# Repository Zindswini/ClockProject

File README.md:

# ClockProject V2.0
This is the GitHub Companion to the Large scale RGB LED Clock as shown in [VIDEO IN PROGRESS]

# Design Files
- 3D and Circuit design was completed using Autodesk Fusion 360. Exports from the project are provided.
- Manufacturing was completed through JLC PCB, Gerber files exported from Fusion 360 are provided.

# Dependencies & Building
This project uses PlatformIO to manage dependencies. In theory, this should mean that you will not have to worry about dependencies and versioning. Just in case, a list of used libraries is provided below.

In order to program your own clock, you need to provide the appropriate credentials for your Wifi network. In order to connect, update the STASSID and STAPSK fields.

This project relies on:
### Libraries:
- [Adafruit ESP8266](https://github.com/adafruit/Adafruit_ESP8266) (In Library Browser)
- [Arduino JSON](https://github.com/bblanchon/ArduinoJson/tree/5.x)  (In Library Browser) (*Note version 5.x*)
- [DHTesp](https://github.com/beegee-tokyo/DHTesp) (In Library Browser)
- [NTPClient](https://github.com/arduino-libraries/NTPClient) (In Library Browser)
- [TelnetStream](https://github.com/jandrassy/TelnetStream) (In Library Browser)

### ESP Board
Add http://arduino.esp8266.com/stable/package_esp8266com_index.json to the "Additional Board Manager URLs" in the Arduino IDE, then add the esp8266 from inside the board manager.

Be sure to select "Adafruit Feather HUZZAH ESP8266" when compiling.

(this might be obsolete now that the project uses PlatformIO)

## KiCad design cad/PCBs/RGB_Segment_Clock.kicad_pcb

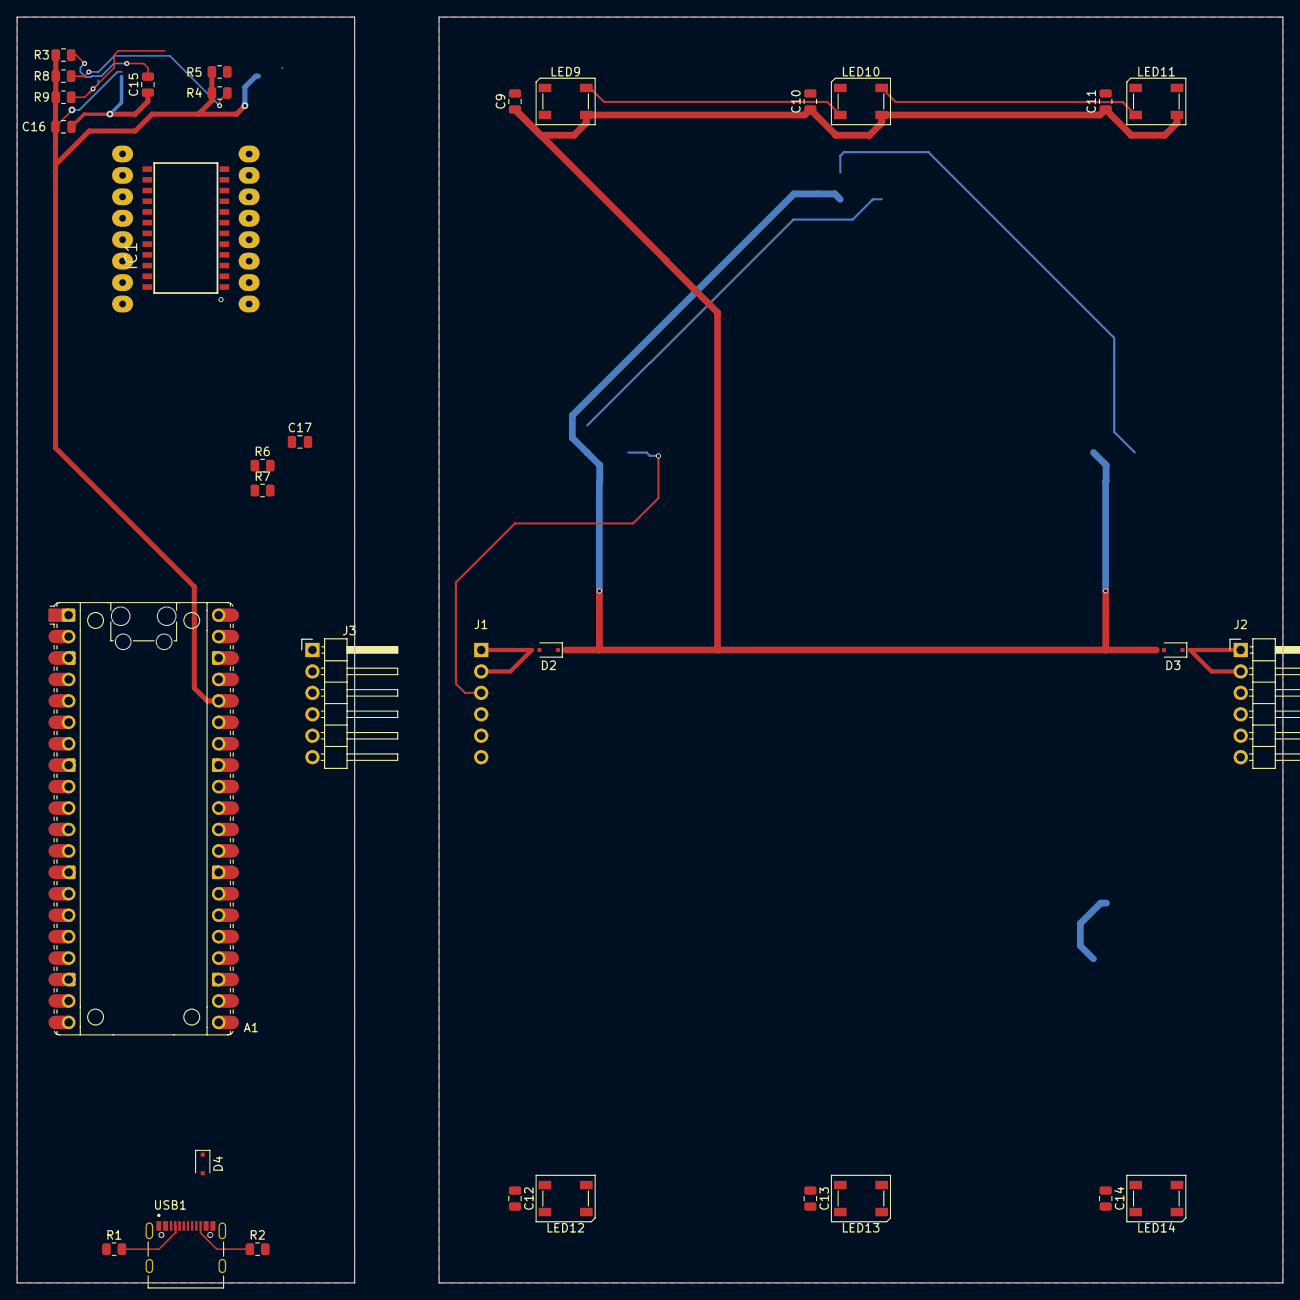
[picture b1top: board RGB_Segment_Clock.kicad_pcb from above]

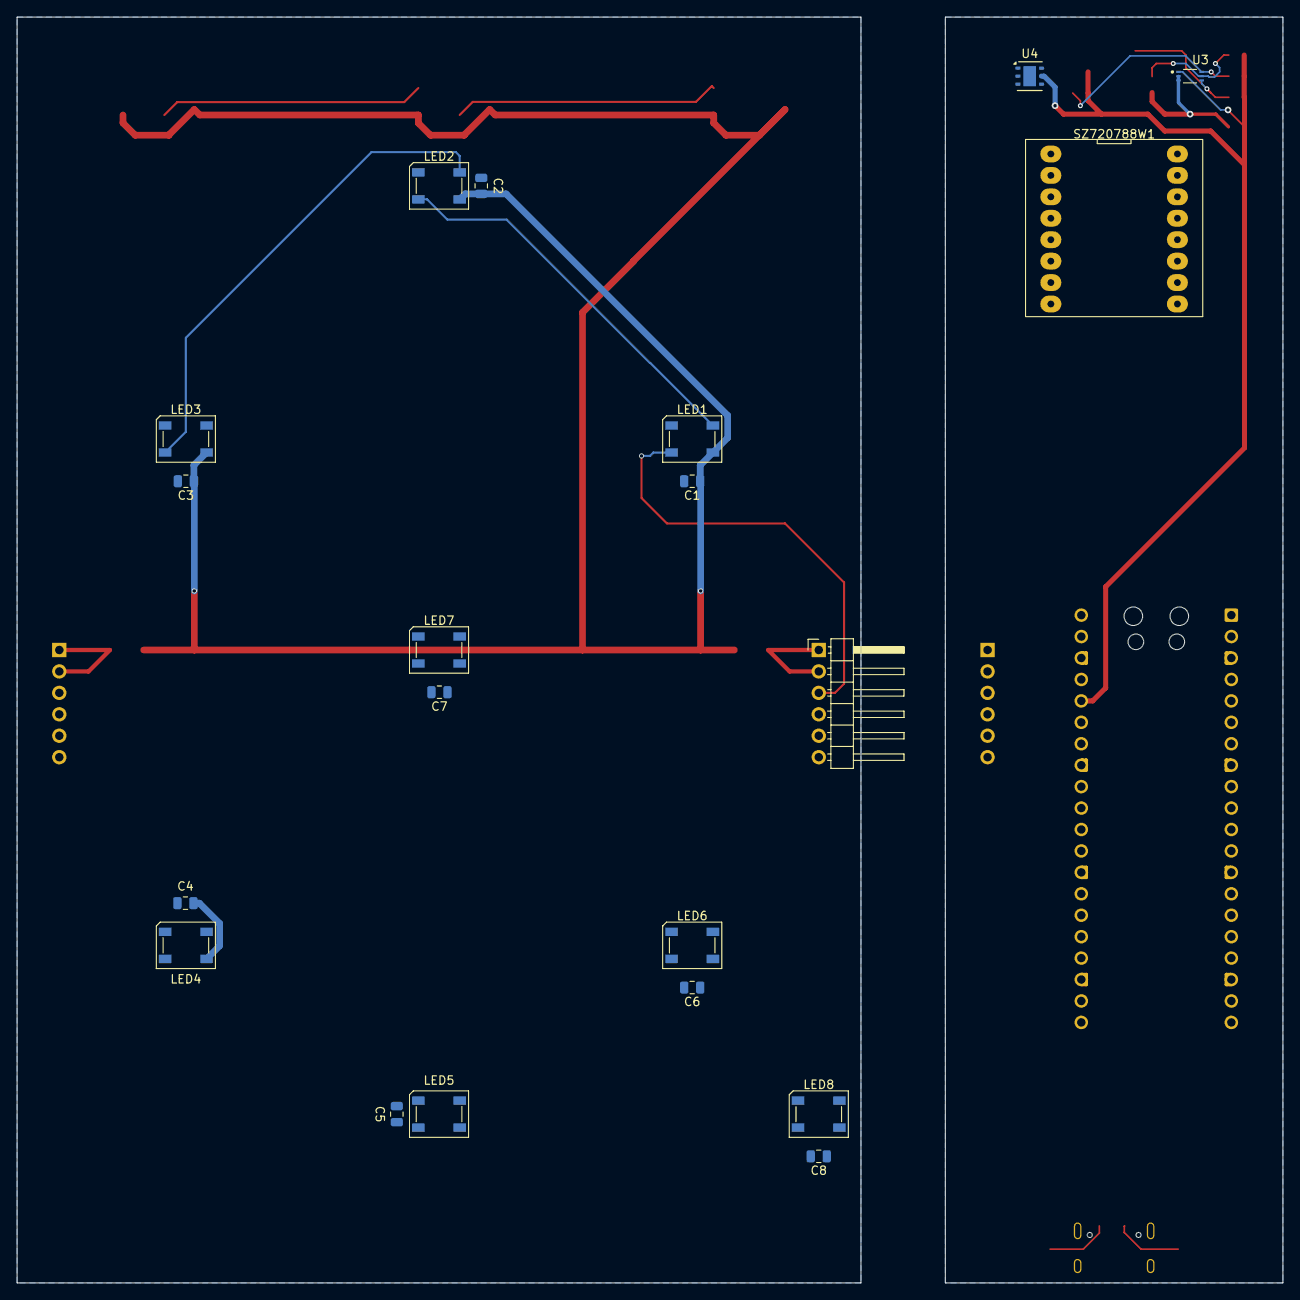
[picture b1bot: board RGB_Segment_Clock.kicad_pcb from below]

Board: 2 copper layers, 150.0 x 150.0 mm, 52 parts (20 on the bottom side), 44 nets.

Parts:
A1: RaspberryPi_Pico_W; RaspberryPi_Pico_Common
C1, C2, C3, C4, C5, C6, C7, C8, C9, C10, C11, C12, C13, C14, C15, C16: 0.1 uF; C_0805_2012Metric
C17: 10uF; C_0805_2012Metric
D2, D3, D4: SS310; D_SOD-323F
IC1: HT16K33
J1: Digit_IN; PinHeader_1x06_P2.54mm_Horizontal
J2: Digit_OUT; PinHeader_1x06_P2.54mm_Horizontal
J3: Controller_Out; PinHeader_1x06_P2.54mm_Horizontal
LED1: DIGIT-A; LED_SK6812_PLCC4_5.0x5.0mm_P3.2mm
LED2: DIGIT-B; LED_SK6812_PLCC4_5.0x5.0mm_P3.2mm
LED3: DIGIT-C; LED_SK6812_PLCC4_5.0x5.0mm_P3.2mm
LED4: DIGIT-D; LED_SK6812_PLCC4_5.0x5.0mm_P3.2mm
LED5: DIGIT-E; LED_SK6812_PLCC4_5.0x5.0mm_P3.2mm
LED6: DIGIT-F; LED_SK6812_PLCC4_5.0x5.0mm_P3.2mm
LED7: DIGIT-G; LED_SK6812_PLCC4_5.0x5.0mm_P3.2mm
LED8: DIGIT-H; LED_SK6812_PLCC4_5.0x5.0mm_P3.2mm
LED9: BL-1; LED_SK6812_PLCC4_5.0x5.0mm_P3.2mm
LED10: BL-2; LED_SK6812_PLCC4_5.0x5.0mm_P3.2mm
LED11: BL-3; LED_SK6812_PLCC4_5.0x5.0mm_P3.2mm
LED12: BL-4; LED_SK6812_PLCC4_5.0x5.0mm_P3.2mm
LED13: BL-5; LED_SK6812_PLCC4_5.0x5.0mm_P3.2mm
LED14: BL-6; LED_SK6812_PLCC4_5.0x5.0mm_P3.2mm
R1, R2: 5.1k; R_0805_2012Metric
R3, R4, R5, R6, R7, R8, R9: 4.7k; R_0805_2012Metric
SZ720788W1: SZ720788W
U3: BH1750FVI-TR; XDCR_BH1750FVI-TR
U4: HDC2080; Texas_PWSON-N6
USB1: TYPE-C-31-M-12; HRO_TYPE-C-31-M-12

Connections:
+3.3V: A1.36 (3V3), C16.1, C17.1, IC1.24 (VDD), R3.1, R4.2, R5.1, R6.1, R7.1, R8.1, R9.2, U3.1 (VCC), U4.5 (VDD)
+5V: A1.39 (VSYS), C1.1, C2.1, C3.1, C4.1, C5.1, C6.1, C7.1, C8.1, C9.1, C10.1, C11.1, C12.1, C13.1, C14.1, D2.1 (K), D2.2 (A), D3.1 (K), D4.1 (K), J1.1, J1.2, J3.1, J3.2, LED1.3 (VDD), LED2.3 (VDD), LED3.3 (VDD), LED4.3 (VDD), LED5.3 (VDD), LED6.3 (VDD), LED7.3 (VDD), LED8.3 (VDD), LED9.3 (VDD), LED10.3 (VDD), LED11.3 (VDD), LED12.3 (VDD), LED13.3 (VDD), LED14.3 (VDD)
/Controller/BL_OUT: A1.22 (GPIO17), J1.4, J3.4, LED9.2 (DIN)
/Controller/DIGIT_OUT: A1.21 (GPIO16), J1.3, J3.3, LED1.2 (DIN)
/Controller/MATRIX_SCL: A1.25 (I2C1_SCL), IC1.22 (SCL), R7.2
/Controller/MATRIX_SDA: A1.24 (I2C1_SDA), IC1.23 (SDA), R6.2
/Controller/SENSOR_SCL: A1.27 (I2C0_SCL), R4.1, R8.2, U3.6 (SCL), U4.6 (SCL)
/Controller/SENSOR_SDA: A1.26 (I2C0_SDA), R5.2, R9.1, U3.4 (SDA), U4.1 (SDA)
/Digit/BL_OUT: J2.4, LED14.4 (DOUT)
/Digit/DIGIT_OUT: J2.3, LED8.4 (DOUT)
/Digit/VCC_OUT: D3.2 (A), J2.1, J2.2
GND: A1.3 (GND), A1.8 (GND), A1.13 (GND), A1.18 (GND), A1.23 (GND), A1.28 (GND), A1.33 (AGND), A1.38 (GND), C1.2, C2.2, C3.2, C4.2, C5.2, C6.2, C7.2, C8.2, C9.2, C10.2, C11.2, C12.2, C13.2, C14.2, C15.1, C16.2, C17.2, IC1.1 (VSS), J1.5, J1.6, J2.5, J2.6, J3.5, J3.6, LED1.1 (VSS), LED2.1 (VSS), LED3.1 (VSS), LED4.1 (VSS), LED5.1 (VSS), LED6.1 (VSS), LED7.1 (VSS), LED8.1 (VSS), LED9.1 (VSS), LED10.1 (VSS), LED11.1 (VSS), LED12.1 (VSS), LED13.1 (VSS), LED14.1 (VSS), R1.1, R2.2, U3.2 (ADDR), U3.3 (GND), U4.2 (GND), U4.3 (ADDR), USB1.A1_B12 (GND), USB1.B1_A12 (GND), USB1.S1 (SHIELD), USB1.S2 (SHIELD), USB1.S3 (SHIELD), USB1.S4 (SHIELD)
unnamed: D4.2 (A), USB1.A4_B9 (VBUS), USB1.B4_A9 (VBUS)
unnamed: IC1.2 (COM0/AD), SZ720788W1.9 (ROW_1)
unnamed: IC1.3 (COM1/KS0), SZ720788W1.14 (ROW_2)
unnamed: IC1.4 (COM2/KS1), SZ720788W1.8 (ROW_3)
unnamed: IC1.5 (COM3/KS2), SZ720788W1.12 (ROW_4)
unnamed: IC1.6 (COM4), SZ720788W1.1 (ROW_5)
unnamed: IC1.7 (COM5), SZ720788W1.7 (ROW_6)
unnamed: IC1.8 (COM6), SZ720788W1.2 (ROW_7)
unnamed: IC1.9 (COM7), SZ720788W1.5 (ROW_8)
unnamed: IC1.21 (ROW0/A1), SZ720788W1.3 (COL_2)
unnamed: IC1.20 (ROW1/A0), SZ720788W1.4 (COL_3)
unnamed: IC1.19 (ROW2/K1), SZ720788W1.10 (COL_4)
unnamed: IC1.18 (ROW3/K2), SZ720788W1.6 (COL_5)
unnamed: IC1.17 (ROW4/K3), SZ720788W1.11 (COL_6)
unnamed: IC1.16 (ROW5/K4), SZ720788W1.15 (COL_7)
unnamed: IC1.15 (ROW6/K5), SZ720788W1.16 (COL_8)
unnamed: IC1.14 (ROW7/K6), SZ720788W1.13 (COL_1)
unnamed: LED1.4 (DOUT), LED2.2 (DIN)
unnamed: LED2.4 (DOUT), LED3.2 (DIN)
unnamed: LED3.4 (DOUT), LED4.2 (DIN)
unnamed: LED4.4 (DOUT), LED5.2 (DIN)
unnamed: LED5.4 (DOUT), LED6.2 (DIN)
unnamed: LED6.4 (DOUT), LED7.2 (DIN)
unnamed: LED7.4 (DOUT), LED8.2 (DIN)
unnamed: LED9.4 (DOUT), LED10.2 (DIN)
unnamed: LED10.4 (DOUT), LED11.2 (DIN)
unnamed: LED11.4 (DOUT), LED12.2 (DIN)
unnamed: LED12.4 (DOUT), LED13.2 (DIN)
unnamed: LED13.4 (DOUT), LED14.2 (DIN)
unnamed: C15.2, R3.2, U3.5 (DVI)
unnamed: R1.2, USB1.A5 (CC1)
unnamed: R2.1, USB1.B5 (CC2)

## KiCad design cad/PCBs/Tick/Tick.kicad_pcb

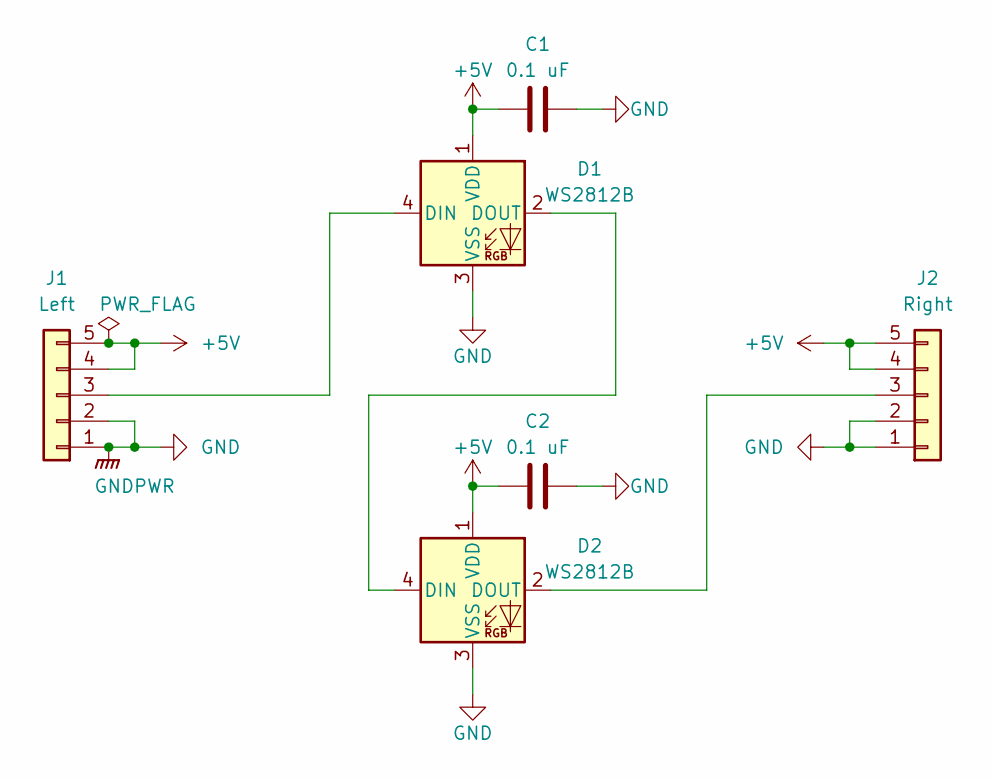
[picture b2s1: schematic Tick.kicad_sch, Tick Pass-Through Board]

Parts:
C1, C2: 0.1 uF; C_0805_2012Metric
D1, D2: WS2812B; LED_WS2812B_PLCC4_5.0x5.0mm_P3.2mm
J1: Left; PinHeader_1x05_P2.54mm_Horizontal
J2: Right; PinHeader_1x05_P2.54mm_Horizontal

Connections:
+5V: C1.2, C2.2, D1.1 (VDD), D2.1 (VDD), J1.4, J1.5, J2.4, J2.5
GND: C1.1, C2.1, D1.3 (VSS), D2.3 (VSS), J1.1, J1.2, J2.1, J2.2
unnamed: D1.2 (DOUT), D2.4 (DIN)
unnamed: D1.4 (DIN), J1.3
unnamed: D2.2 (DOUT), J2.3

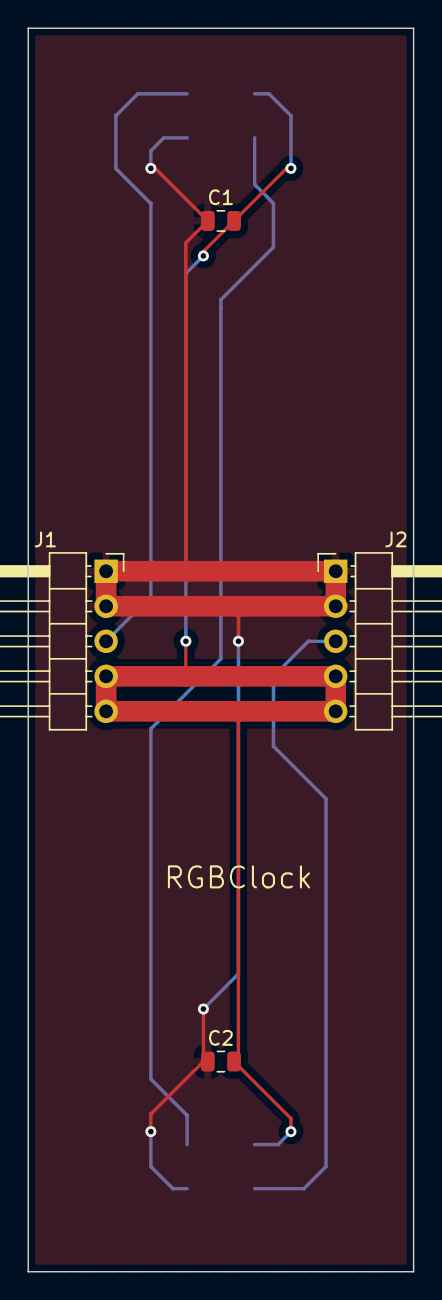
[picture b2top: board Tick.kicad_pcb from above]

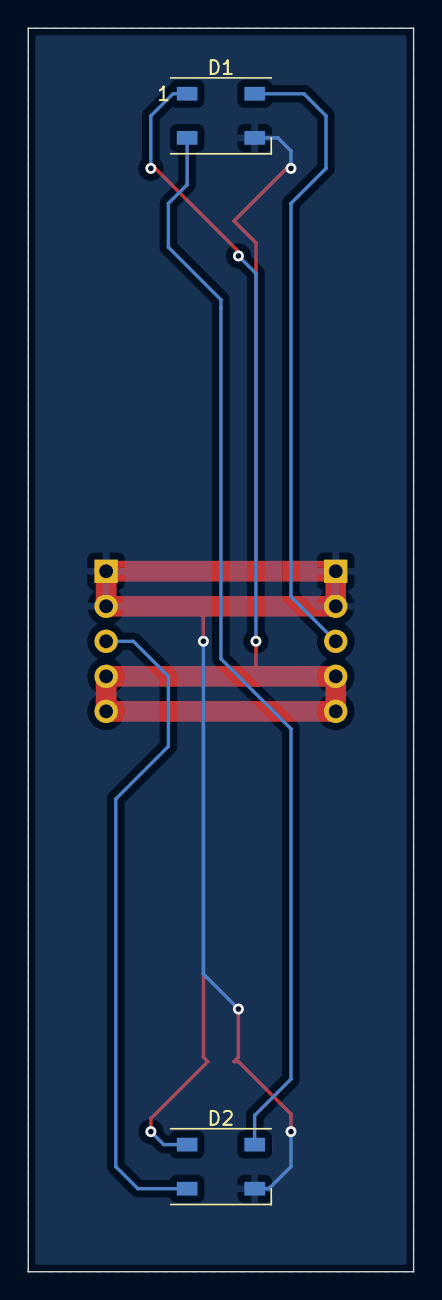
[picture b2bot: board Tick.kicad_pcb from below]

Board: 2 copper layers, 27.9 x 90.2 mm, 6 parts (2 on the bottom side), 5 nets.

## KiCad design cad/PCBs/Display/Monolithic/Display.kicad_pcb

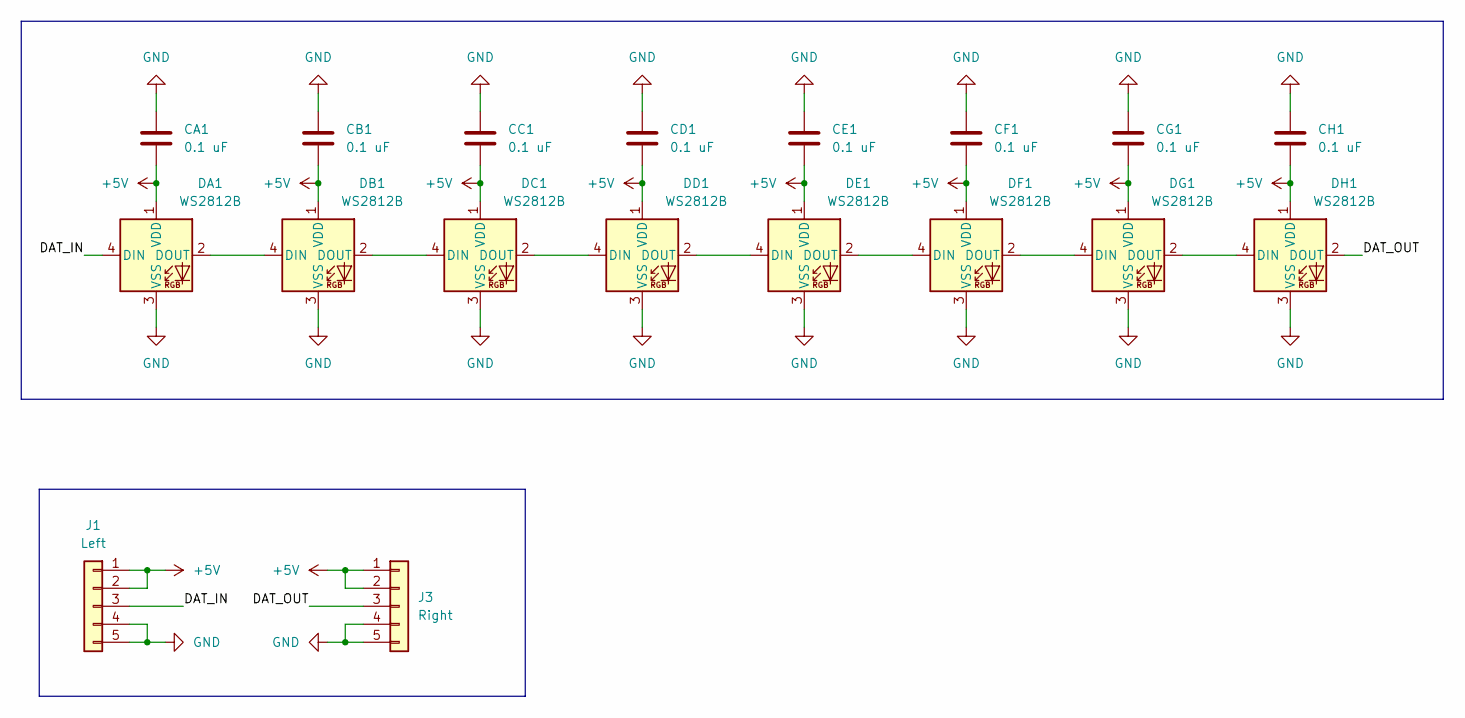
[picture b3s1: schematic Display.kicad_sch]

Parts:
CA1: 0.1 uF; C_0805_2012Metric
CB1: 0.1 uF; C_0805_2012Metric
CC1: 0.1 uF; C_0805_2012Metric
CD1: 0.1 uF; C_0805_2012Metric
CE1: 0.1 uF; C_0805_2012Metric
CF1: 0.1 uF; C_0805_2012Metric
CG1: 0.1 uF; C_0805_2012Metric
CH1: 0.1 uF; C_0805_2012Metric
DA1: WS2812B; LED_WS2812B_PLCC4_5.0x5.0mm_P3.2mm
DB1: WS2812B; LED_WS2812B_PLCC4_5.0x5.0mm_P3.2mm
DC1: WS2812B; LED_WS2812B_PLCC4_5.0x5.0mm_P3.2mm
DD1: WS2812B; LED_WS2812B_PLCC4_5.0x5.0mm_P3.2mm
DE1: WS2812B; LED_WS2812B_PLCC4_5.0x5.0mm_P3.2mm
DF1: WS2812B; LED_WS2812B_PLCC4_5.0x5.0mm_P3.2mm
DG1: WS2812B; LED_WS2812B_PLCC4_5.0x5.0mm_P3.2mm
DH1: WS2812B; LED_WS2812B_PLCC4_5.0x5.0mm_P3.2mm
J1: Left; PinHeader_1x05_P2.54mm_Horizontal
J3: Right; PinHeader_1x05_P2.54mm_Horizontal

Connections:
+5V: CA1.2, CB1.2, CC1.2, CD1.2, CE1.2, CF1.2, CG1.2, CH1.2, DA1.1 (VDD), DB1.1 (VDD), DC1.1 (VDD), DD1.1 (VDD), DE1.1 (VDD), DF1.1 (VDD), DG1.1 (VDD), DH1.1 (VDD), J1.1, J1.2, J3.1, J3.2
/DAT_IN: DA1.4 (DIN), J1.3
/DAT_OUT: DH1.2 (DOUT), J3.3
GND: CA1.1, CB1.1, CC1.1, CD1.1, CE1.1, CF1.1, CG1.1, CH1.1, DA1.3 (VSS), DB1.3 (VSS), DC1.3 (VSS), DD1.3 (VSS), DE1.3 (VSS), DF1.3 (VSS), DG1.3 (VSS), DH1.3 (VSS), J1.4, J1.5, J3.4, J3.5
unnamed: DA1.2 (DOUT), DB1.4 (DIN)
unnamed: DB1.2 (DOUT), DC1.4 (DIN)
unnamed: DC1.2 (DOUT), DD1.4 (DIN)
unnamed: DD1.2 (DOUT), DE1.4 (DIN)
unnamed: DE1.2 (DOUT), DF1.4 (DIN)
unnamed: DF1.2 (DOUT), DG1.4 (DIN)
unnamed: DG1.2 (DOUT), DH1.4 (DIN)

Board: 2 copper layers, 18 parts (0 on the bottom side), 11 nets, no tracks yet.

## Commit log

2020-07-26 Initial Files
2020-07-26 Add Pictures
2020-07-27 Images, Readme, Eagle files, Fusion files, STLs
2020-07-27 12hr support, fixed night modes
2021-01-26 Fix Spelling
2022-01-04 Fix images after branch rename
2022-01-04 Add PlatformIO Build
    Also moved functions around to make the C++ work
2022-05-26 Restructure files, init KiCad projects
2022-06-28 Initial work in Kicad and OpenSCAD
2022-07-14 Display CAD Progress
2023-10-15 Cleanup old file, test sync
2024-12-23 Add gitignore and pi pico KiCad submodule
2024-12-23 Initial work on importing necessary KiCad Libraries
2024-12-23 Add FreeCAD backup files to gitignore
2024-12-23 Initial Digit Schematic and Layout
2024-12-23 Initial Digit Component Placement
2024-12-27 Connected Controller Components, updated matrix footprint
2024-12-27 WIP Routing Controller
2024-12-27 Add some part+datasheet links to docs folder
2024-12-27 Remove .obsidian folder from git
2024-12-27 Add .obsidian to gitignore
2024-12-27 WIP Integrating USB C PD
2024-12-30 Move Power Circuit to sub schematic
2024-12-30 Finish schematic for PD Controller
